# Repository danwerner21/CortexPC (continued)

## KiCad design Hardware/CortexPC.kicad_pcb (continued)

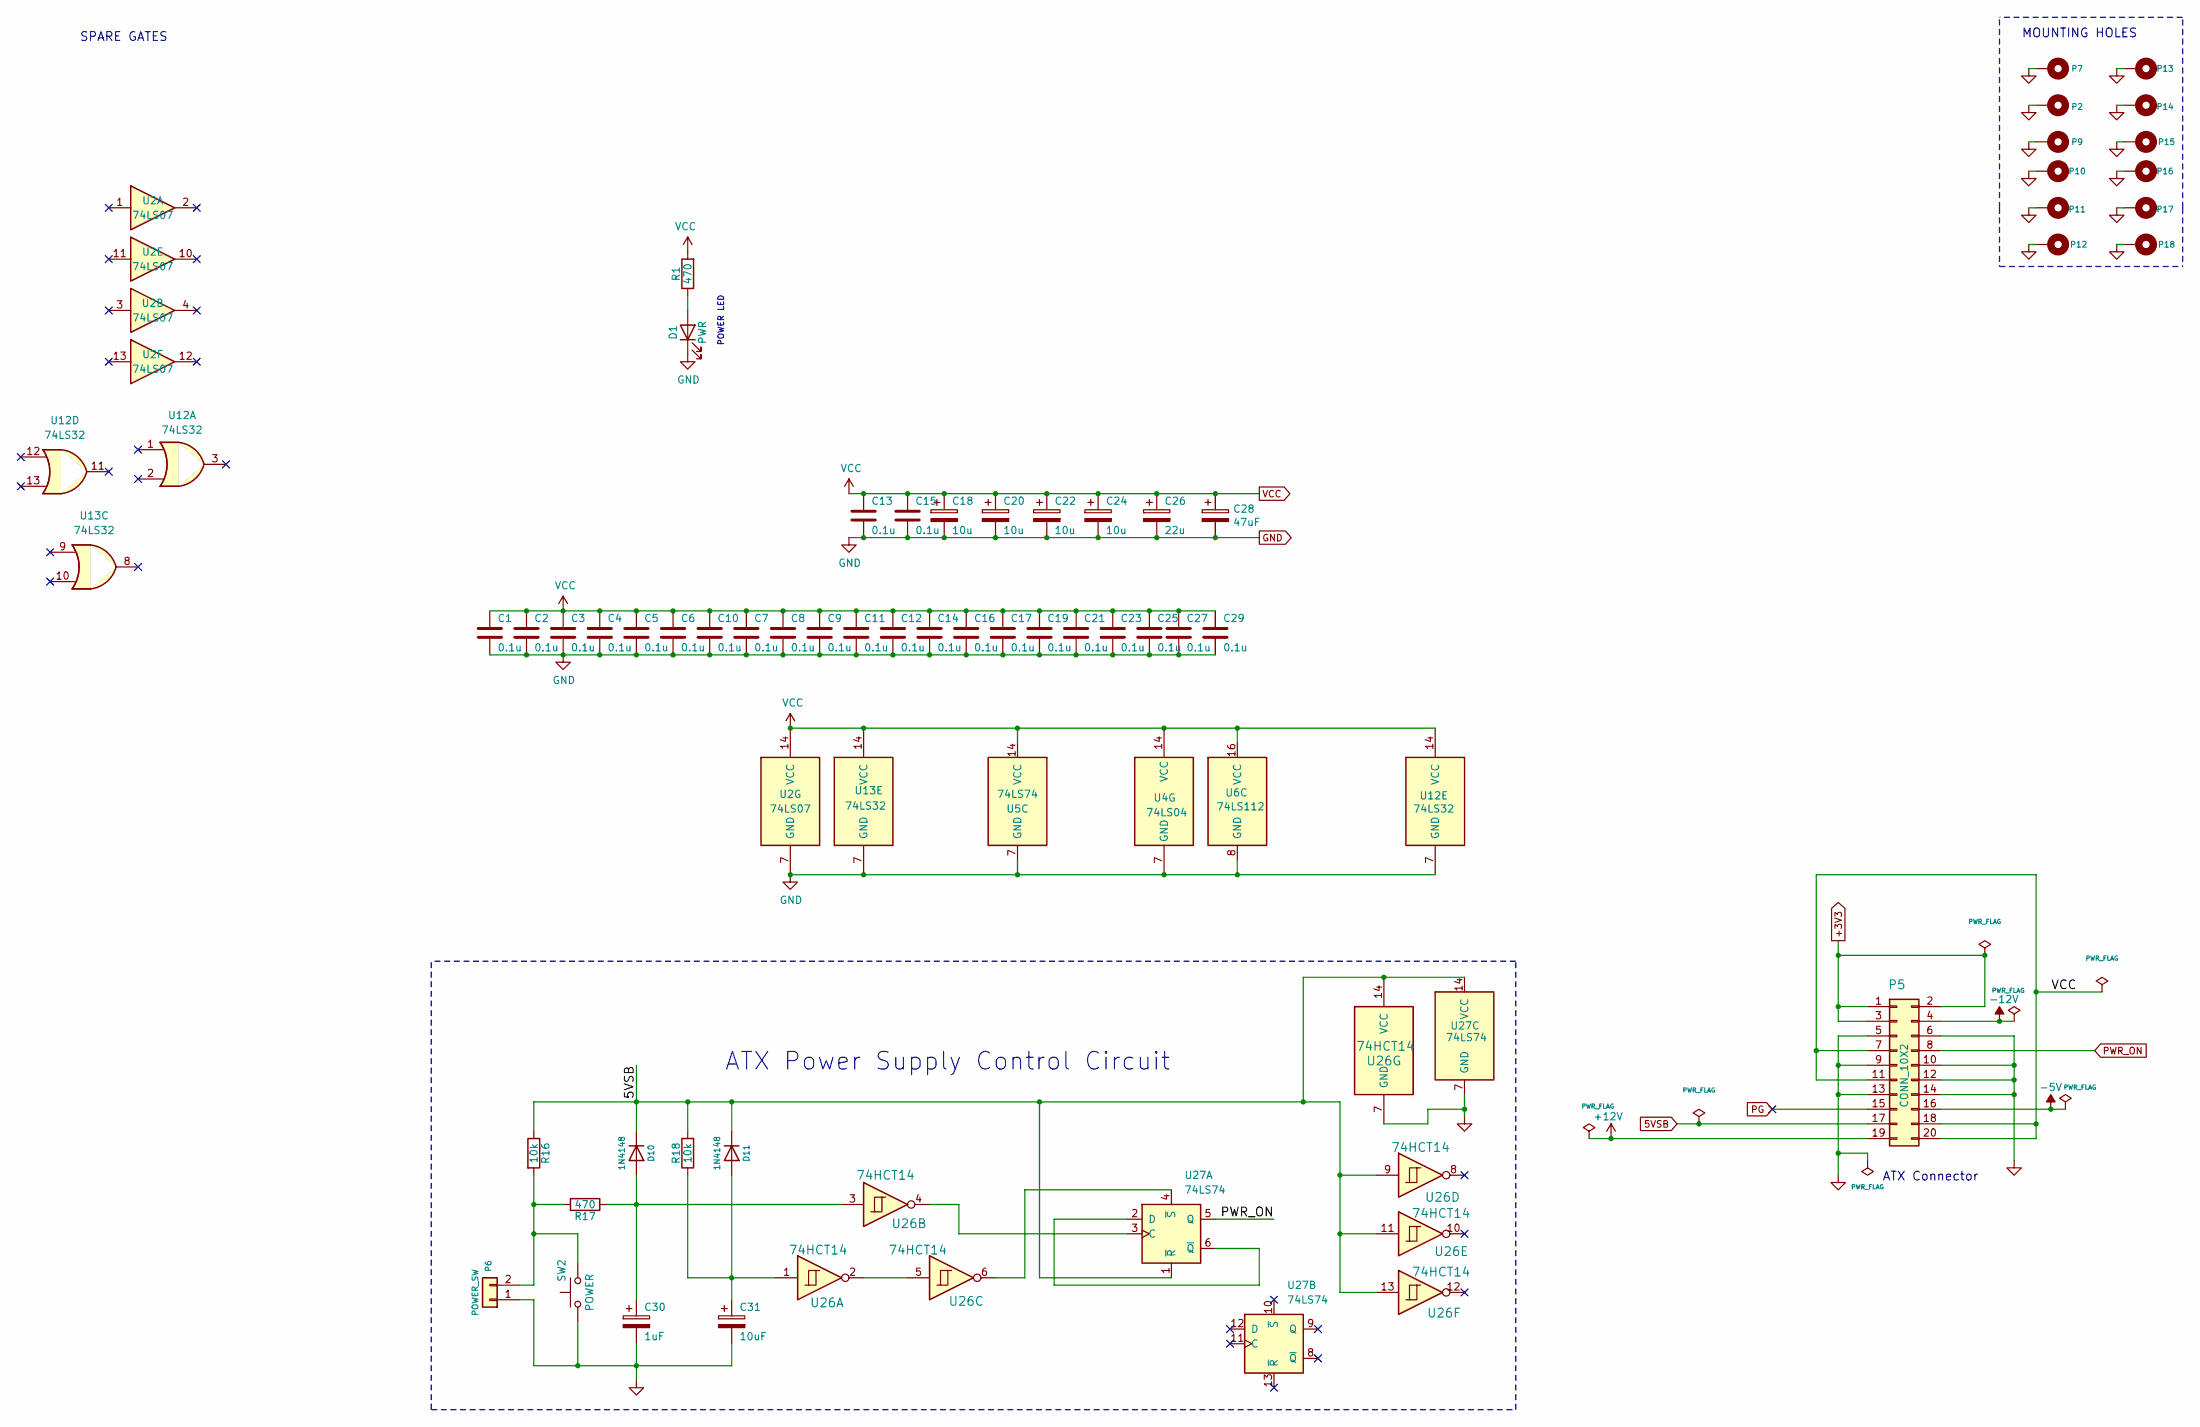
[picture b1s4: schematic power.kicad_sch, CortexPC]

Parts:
C1, C2, C3, C4, C5, C6, C7, C8, C9, C10, C11, C12, C13, C14, C15, C16, C17, C19, C21, C23, C25, C27, C29: 0.1u; STD_DDW_CAP
C18, C20, C22, C24: 10u; STD_DDW_PCAP
C26: 22u; STD_DDW_PCAP
C28: 47uF; STD_DDW_PCAP
C30: 1uF; STD_DDW_PCAP
C31: 10uF; STD_DDW_PCAP
D1: PWR; STD_DDW_LED5
D10, D11: 1N4148; STD_DDW_DIODE
P2, P7, P9, P10, P11, P12, P13, P14, P15, P16, P17, P18: CONN_1; MountingHole_3.2mm_M3_Pad_TopBottom
P5: CONN_10X2; ATXConnector
P6: POWER_SW; STD_DDW_PINHEAD_V_1x02
R1, R17: 470; STD_DDW_RESISTOR
R16, R18: 10k; STD_DDW_RESISTOR
SW2: POWER; STD_DDW_TACTSW
U2: 74LS07; STD_DDW_DIP14
U4: 74LS04; STD_DDW_DIP14
U5, U27: 74LS74; STD_DDW_DIP14
U6: 74LS112; STD_DDW_DIP16
U12, U13: 74LS32; STD_DDW_DIP14
U26: 74HCT14; STD_DDW_DIP14

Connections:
5VSB: D10.1 (K), D11.1 (K), P5.17, R16.1, R18.2, U26.9, U26.11, U26.13, U26.14 (VCC), U27.1 (~R), U27.14 (VCC)
+3V3: P5.1, P5.2, P5.3
+12V: P5.19; also elsewhere on the board
-5V: P5.16; also elsewhere on the board
-12V: P5.4; also elsewhere on the board
GND: C1.2, C2.2, C3.2, C4.2, C5.2, C6.2, C7.2, C8.2, C9.2, C10.2, C11.2, C12.2, C13.2, C14.2, C15.2, C16.2, C17.2, C18.2, C19.2, C20.2, C21.2, C22.2, C23.2, C24.2, C25.2, C26.2, C27.2, C28.2, C29.2, C30.2, C31.2, D1.1 (K), P2.1, P5.5, P5.6, P5.9, P5.10, P5.12, P5.13, P5.14, P6.1, P7.1, P9.1, P10.1, P11.1, P12.1, P13.1, P14.1, P15.1, P16.1, P17.1, P18.1, SW2.1, U2.7 (GND), U4.7 (GND), U5.7 (GND), U6.8 (GND), U12.7 (GND), U13.7 (GND), U26.7 (GND), U27.7 (GND); also elsewhere on the board
unnamed: D1.2 (A), R1.1
unnamed: C30.1, D10.2 (A), R17.1, U26.3
unnamed: C31.1, D11.2 (A), R18.1, U26.1
unnamed: P6.2, R16.2, R17.2, SW2.2
unnamed: U26.2, U26.5
unnamed: U26.4, U27.3 (C)
unnamed: U27.2 (D), U27.6 (~Q)
unnamed: U26.6, U27.4 (~S)
PG: P5.15
PWR_ON: P5.8, U27.5 (Q)
VCC: C1.1, C2.1, C3.1, C4.1, C5.1, C6.1, C7.1, C8.1, C9.1, C10.1, C11.1, C12.1, C13.1, C14.1, C15.1, C16.1, C17.1, C18.1, C19.1, C20.1, C21.1, C22.1, C23.1, C24.1, C25.1, C26.1, C27.1, C28.1, C29.1, P5.7, P5.11, P5.18, P5.20, R1.2, U2.14 (VCC), U4.14 (VCC), U5.14 (VCC), U6.16 (VCC), U12.14 (VCC), U13.14 (VCC); also elsewhere on the board

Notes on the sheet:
POWER LED
ATX Power Supply Control Circuit
MOUNTING HOLES
SPARE GATES
ATX Connector

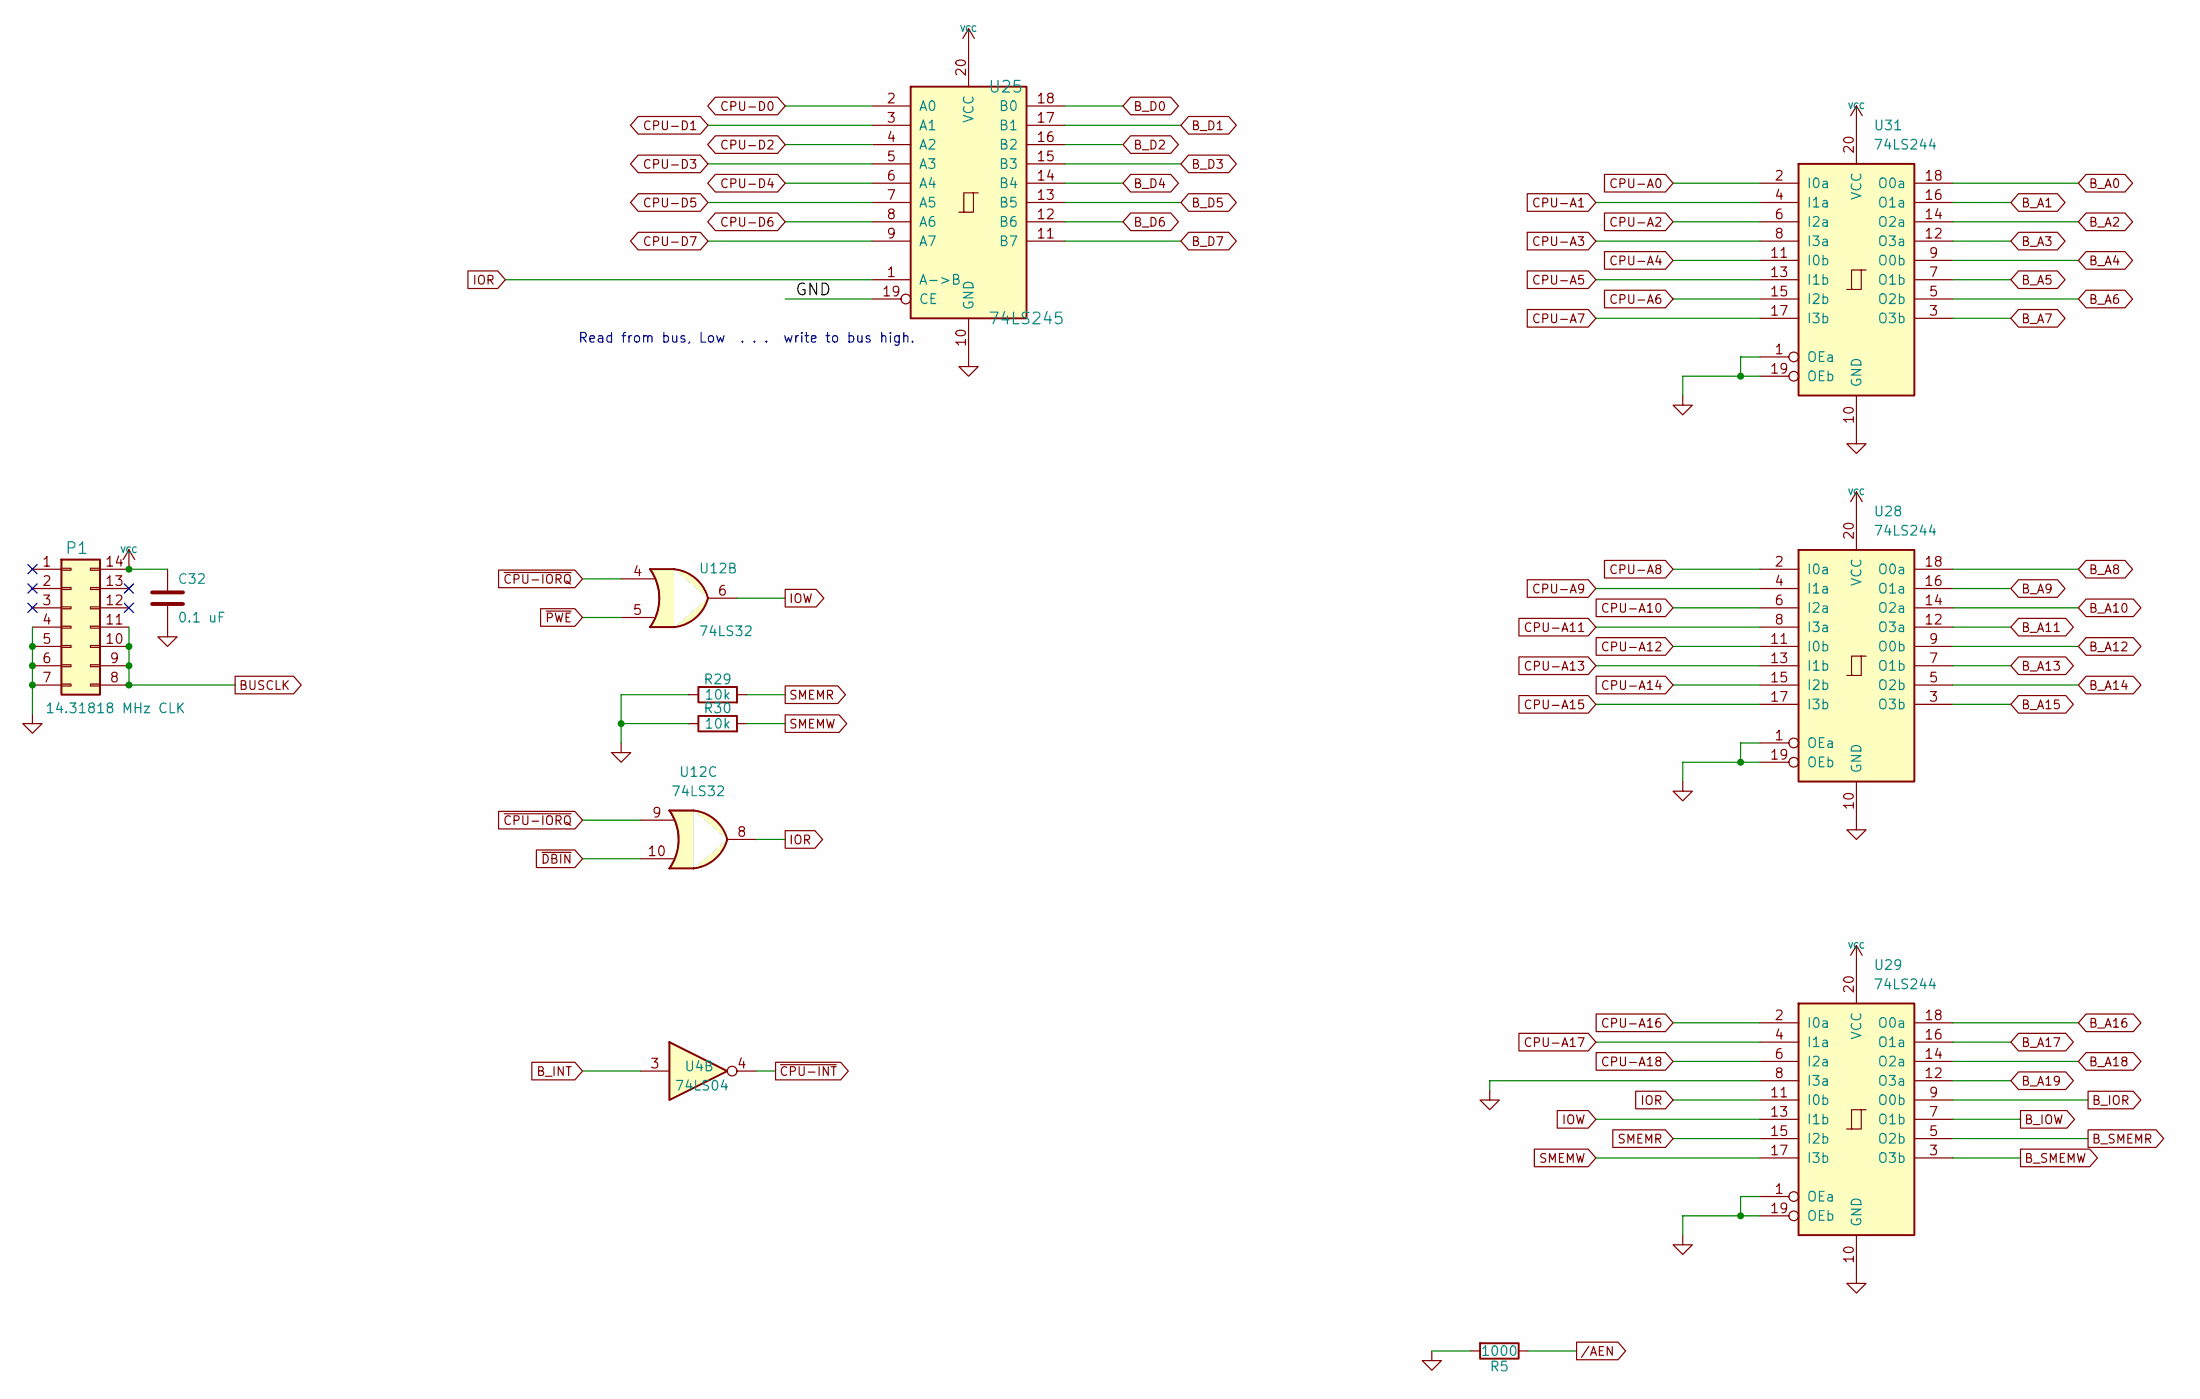
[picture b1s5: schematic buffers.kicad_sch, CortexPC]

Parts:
C32: 0.1 uF; STD_DDW_CAP
P1: 14.31818 MHz CLK; STD_DDW_DIP14
R5: 1000; STD_DDW_RESISTOR
R29, R30: 10k; STD_DDW_RESISTOR
U4: 74LS04; STD_DDW_DIP14
U12: 74LS32; STD_DDW_DIP14
U25: 74LS245; STD_DDW_DIP20
U28, U29, U31: 74LS244; STD_DDW_DIP20

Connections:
BUSCLK: P1.8, P1.9, P1.10, P1.11; also elsewhere on the board
B_A0: U31.18 (O0a); also elsewhere on the board
B_A1: U31.16 (O1a); also elsewhere on the board
B_A2: U31.14 (O2a); also elsewhere on the board
B_A3: U31.12 (O3a); also elsewhere on the board
B_A4: U31.9 (O0b); also elsewhere on the board
B_A5: U31.7 (O1b); also elsewhere on the board
B_A6: U31.5 (O2b); also elsewhere on the board
B_A7: U31.3 (O3b); also elsewhere on the board
B_A8: U28.18 (O0a); also elsewhere on the board
B_A9: U28.16 (O1a); also elsewhere on the board
B_A10: U28.14 (O2a); also elsewhere on the board
B_A11: U28.12 (O3a); also elsewhere on the board
B_A12: U28.9 (O0b); also elsewhere on the board
B_A13: U28.7 (O1b); also elsewhere on the board
B_A14: U28.5 (O2b); also elsewhere on the board
B_A15: U28.3 (O3b); also elsewhere on the board
B_A16: U29.18 (O0a); also elsewhere on the board
B_A17: U29.16 (O1a); also elsewhere on the board
B_A18: U29.14 (O2a); also elsewhere on the board
B_A19: U29.12 (O3a); also elsewhere on the board
B_D0: U25.18 (B0); also elsewhere on the board
B_D1: U25.17 (B1); also elsewhere on the board
B_D2: U25.16 (B2); also elsewhere on the board
B_D3: U25.15 (B3); also elsewhere on the board
B_D4: U25.14 (B4); also elsewhere on the board
B_D5: U25.13 (B5); also elsewhere on the board
B_D6: U25.12 (B6); also elsewhere on the board
B_D7: U25.11 (B7); also elsewhere on the board
B_INT: U4.3; also elsewhere on the board
B_IOR: U29.9 (O0b); also elsewhere on the board
B_IOW: U29.7 (O1b); also elsewhere on the board
B_SMEMR: U29.5 (O2b); also elsewhere on the board
B_SMEMW: U29.3 (O3b); also elsewhere on the board
CPU-A0: U31.2 (I0a); also elsewhere on the board
CPU-A1: U31.4 (I1a); also elsewhere on the board
CPU-A2: U31.6 (I2a); also elsewhere on the board
CPU-A3: U31.8 (I3a); also elsewhere on the board
CPU-A4: U31.11 (I0b); also elsewhere on the board
CPU-A5: U31.13 (I1b); also elsewhere on the board
CPU-A6: U31.15 (I2b); also elsewhere on the board
CPU-A7: U31.17 (I3b); also elsewhere on the board
CPU-A8: U28.2 (I0a); also elsewhere on the board
CPU-A9: U28.4 (I1a); also elsewhere on the board
CPU-A10: U28.6 (I2a); also elsewhere on the board
CPU-A11: U28.8 (I3a); also elsewhere on the board
CPU-A12: U28.11 (I0b); also elsewhere on the board
CPU-A13: U28.13 (I1b); also elsewhere on the board
CPU-A14: U28.15 (I2b); also elsewhere on the board
CPU-A15: U28.17 (I3b); also elsewhere on the board
CPU-A16: U29.2 (I0a); also elsewhere on the board
CPU-A17: U29.4 (I1a); also elsewhere on the board
CPU-A18: U29.6 (I2a); also elsewhere on the board
CPU-D0: U25.2 (A0); also elsewhere on the board
CPU-D1: U25.3 (A1); also elsewhere on the board
CPU-D2: U25.4 (A2); also elsewhere on the board
CPU-D3: U25.5 (A3); also elsewhere on the board
CPU-D4: U25.6 (A4); also elsewhere on the board
CPU-D5: U25.7 (A5); also elsewhere on the board
CPU-D6: U25.8 (A6); also elsewhere on the board
CPU-D7: U25.9 (A7); also elsewhere on the board
GND: C32.2, P1.4, P1.5, P1.6, P1.7, R5.2, R29.1, R30.1, U25.10 (GND), U25.19 (CE), U28.1 (OEa), U28.10 (GND), U28.19 (OEb), U29.1 (OEa), U29.8 (I3a), U29.10 (GND), U29.19 (OEb), U31.1 (OEa), U31.10 (GND), U31.19 (OEb); also elsewhere on the board
IOR: U12.8, U25.1 (A->B), U29.11 (I0b)
IOW: U12.6, U29.13 (I1b)
SMEMR: R29.2, U29.15 (I2b)
SMEMW: R30.2, U29.17 (I3b)
VCC: C32.1, P1.14, U25.20 (VCC), U28.20 (VCC), U29.20 (VCC), U31.20 (VCC); also elsewhere on the board
/AEN: R5.1; also elsewhere on the board
~CPU-INT: U4.4; also elsewhere on the board
~CPU-IORQ: U12.4, U12.9; also elsewhere on the board
~DBIN: U12.10; also elsewhere on the board
~PWE: U12.5; also elsewhere on the board

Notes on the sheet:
Read from bus, Low . . . write to bus high.

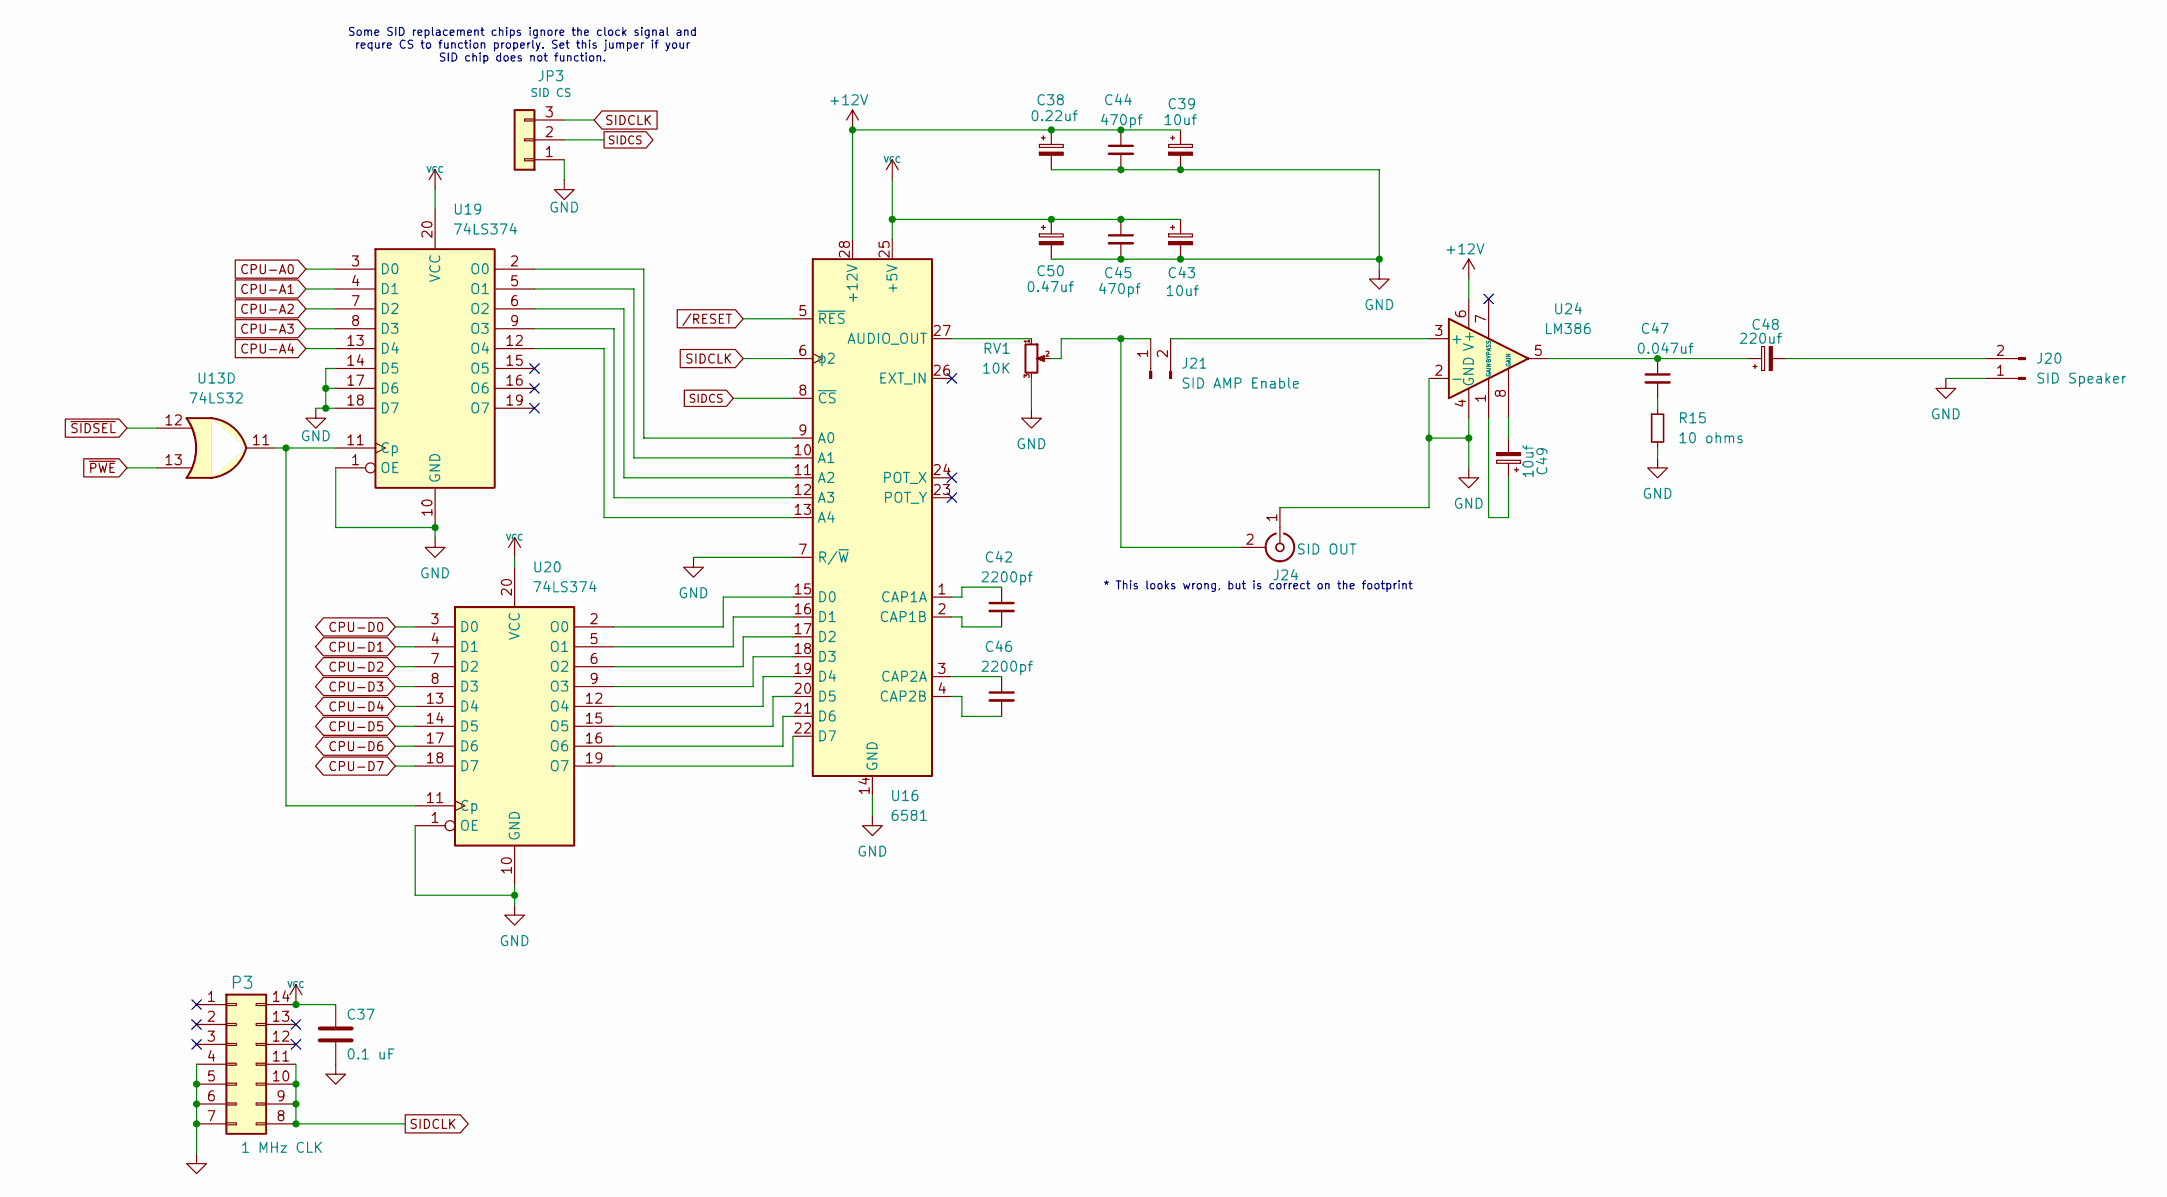
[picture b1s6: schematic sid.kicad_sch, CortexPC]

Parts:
C37: 0.1 uF; STD_DDW_CAP
C38: 0.22uf; STD_DDW_PCAP
C39, C43, C49: 10uf; STD_DDW_PCAP
C42, C46: 2200pf; STD_DDW_CAP
C44, C45: 470pf; STD_DDW_CAP
C47: 0.047uf; STD_DDW_CAP
C48: 220uf; STD_DDW_PCAP
C50: 0.47uf; STD_DDW_PCAP
J20: SID Speaker; STD_DDW_PINHEAD_V_1x02
J21: SID AMP Enable; STD_DDW_PINHEAD_V_1x02
J24: SID OUT; CUI_RCJ-047
JP3: SID CS; STD_DDW_PINHEAD_V_1x03
P3: 1 MHz CLK; STD_DDW_DIP14
R15: 10 ohms; STD_DDW_RESISTOR
RV1: 10K; Potentiometer_Bourns_3386F_Vertical
U13: 74LS32; STD_DDW_DIP14
U16: 6581; STD_DDW_DIP28
U19, U20: 74LS374; STD_DDW_DIP20
U24: LM386; STD_DDW_DIP8

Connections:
+12V: C38.1, C39.1, C44.1, U16.28 (+12V), U24.6 (V+); also elsewhere on the board
CPU-A0: U19.3 (D0); also elsewhere on the board
CPU-A1: U19.4 (D1); also elsewhere on the board
CPU-A2: U19.7 (D2); also elsewhere on the board
CPU-A3: U19.8 (D3); also elsewhere on the board
CPU-A4: U19.13 (D4); also elsewhere on the board
CPU-D0: U20.3 (D0); also elsewhere on the board
CPU-D1: U20.4 (D1); also elsewhere on the board
CPU-D2: U20.7 (D2); also elsewhere on the board
CPU-D3: U20.8 (D3); also elsewhere on the board
CPU-D4: U20.13 (D4); also elsewhere on the board
CPU-D5: U20.14 (D5); also elsewhere on the board
CPU-D6: U20.17 (D6); also elsewhere on the board
CPU-D7: U20.18 (D7); also elsewhere on the board
GND: C37.2, C38.2, C39.2, C43.2, C44.2, C45.2, C50.2, J20.1, J24.1 (In), JP3.1, P3.4, P3.5, P3.6, P3.7, R15.2, RV1.3, U16.7 (R/~W), U16.14 (GND), U19.1 (OE), U19.10 (GND), U19.14 (D5), U19.17 (D6), U19.18 (D7), U20.1 (OE), U20.10 (GND), U24.2 (-), U24.4 (GND); also elsewhere on the board
unnamed: C47.1, C48.1, U24.5
unnamed: C47.2, R15.1
unnamed: C49.1, U24.1 (GAIN)
unnamed: C49.2, U24.8 (GAIN)
unnamed: C48.2, J20.2
unnamed: J21.1, J24.2 (Ext), RV1.2
unnamed: J21.2, U24.3 (+)
unnamed: U16.9 (A0), U19.2 (O0)
unnamed: U16.10 (A1), U19.5 (O1)
unnamed: U16.11 (A2), U19.6 (O2)
unnamed: U16.12 (A3), U19.9 (O3)
unnamed: U16.13 (A4), U19.12 (O4)
unnamed: RV1.1, U16.27 (AUDIO_OUT)
unnamed: C42.1, U16.1 (CAP1A)
unnamed: C42.2, U16.2 (CAP1B)
unnamed: C46.1, U16.3 (CAP2A)
unnamed: C46.2, U16.4 (CAP2B)
unnamed: U16.15 (D0), U20.2 (O0)
unnamed: U16.16 (D1), U20.5 (O1)
unnamed: U16.17 (D2), U20.6 (O2)
unnamed: U16.18 (D3), U20.9 (O3)
unnamed: U16.19 (D4), U20.12 (O4)
unnamed: U16.20 (D5), U20.15 (O5)
unnamed: U16.21 (D6), U20.16 (O6)
unnamed: U16.22 (D7), U20.19 (O7)
unnamed: U13.11, U19.11 (Cp), U20.11 (Cp)
SIDCLK: JP3.3, P3.8, P3.9, P3.10, P3.11, U16.6 (ϕ2)
SIDCS: JP3.2, U16.8 (~CS)
VCC: C37.1, C43.1, C45.1, C50.1, P3.14, U16.25 (+5V), U19.20 (VCC), U20.20 (VCC); also elsewhere on the board
/RESET: U16.5 (~RES); also elsewhere on the board
~PWE: U13.13; also elsewhere on the board
~SIDSEL: U13.12; also elsewhere on the board

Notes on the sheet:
Some SID replacement chips ignore the clock signal and requre CS to function properly. Set this jumper if your SID chip does not function.
* This looks wrong, but is correct on the footprint

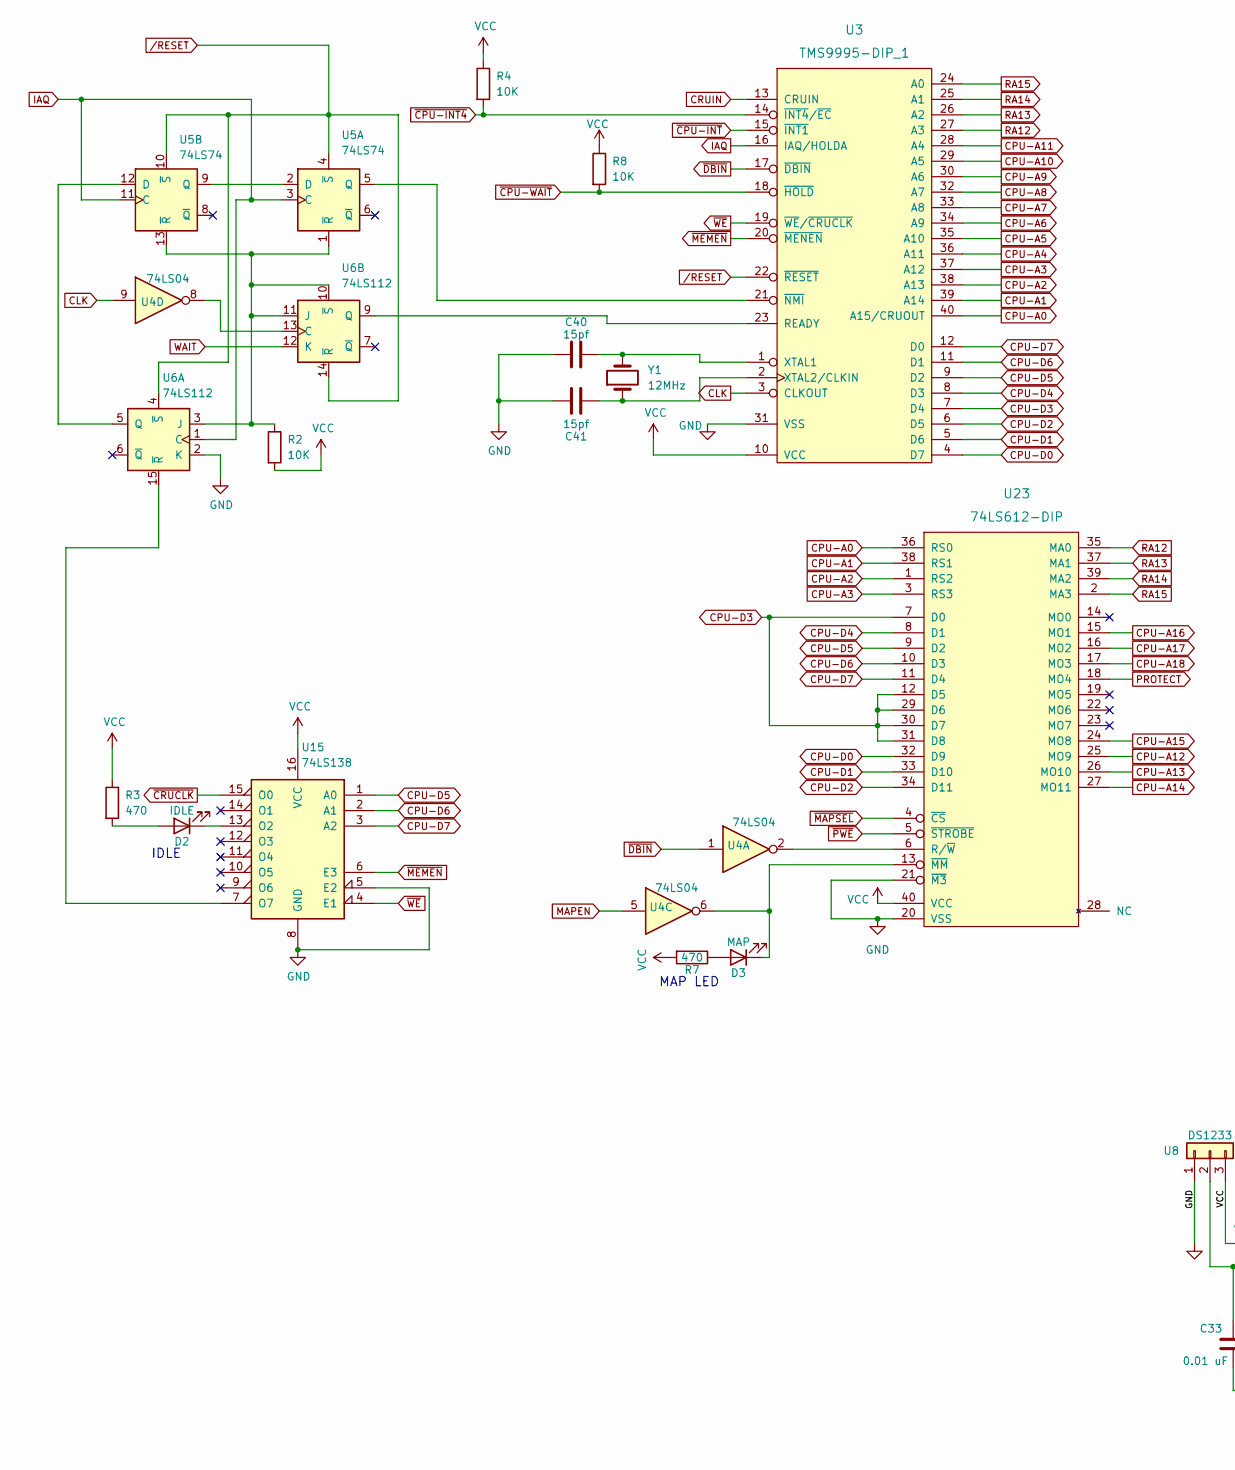
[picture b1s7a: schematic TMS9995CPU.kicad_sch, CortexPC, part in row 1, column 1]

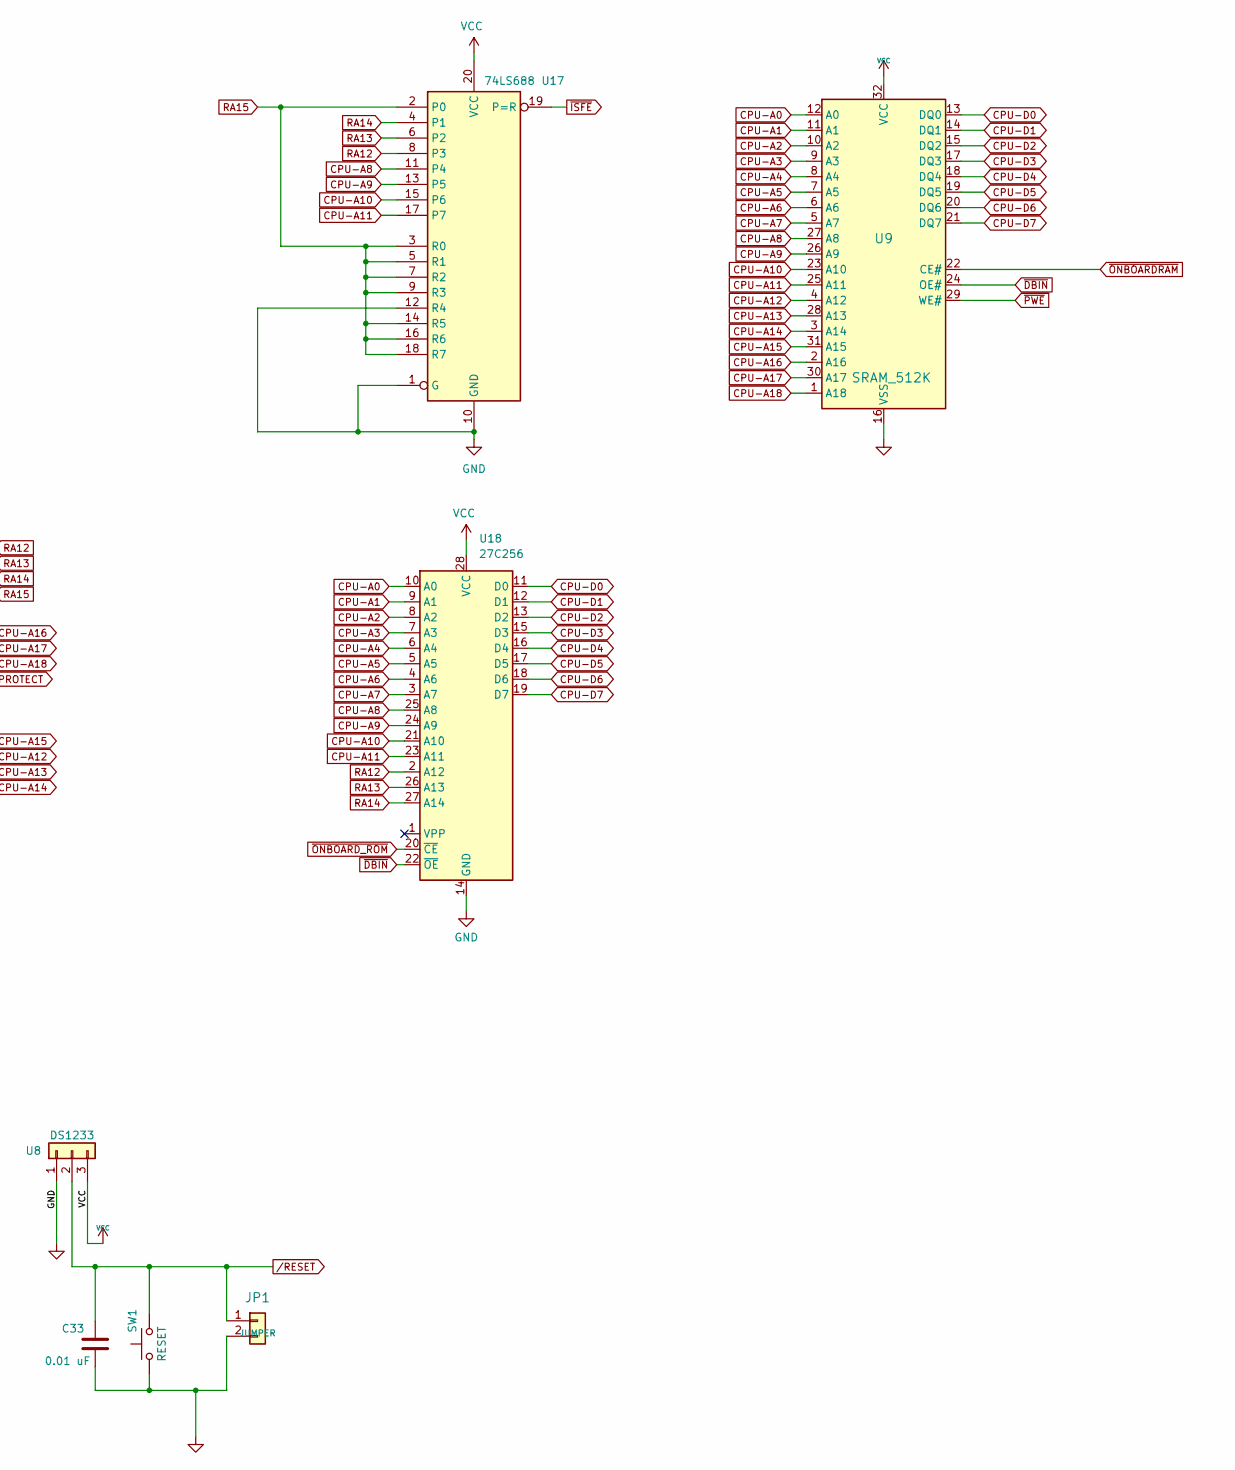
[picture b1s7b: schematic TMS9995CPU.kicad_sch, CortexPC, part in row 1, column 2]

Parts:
C33: 0.01 uF; STD_DDW_CAP
C40, C41: 15pf; STD_DDW_CAP
D2: IDLE; STD_DDW_LED5
D3: MAP; STD_DDW_LED5
JP1: JUMPER; STD_DDW_PINHEAD_V_1x02
R2, R4, R8: 10K; STD_DDW_RESISTOR
R3, R7: 470; STD_DDW_RESISTOR
SW1: RESET; STD_DDW_TACTSW
U3: TMS9995-DIP_1; STD_DDW_DIP40
U4: 74LS04; STD_DDW_DIP14
U5: 74LS74; STD_DDW_DIP14
U6: 74LS112; STD_DDW_DIP16
U8: DS1233; STD_DDW_TO92
U9: SRAM_512K; STD_DDW_DIP32
U15: 74LS138; STD_DDW_DIP16
U17: 74LS688; STD_DDW_DIP20
U18: 27C256; STD_DDW_DIP28
U23: 74LS612-DIP; STD_DDW_DIP40
Y1: 12MHz; STD_DDW_XTAL

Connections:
CLK: U3.3 (CLKOUT), U4.9; also elsewhere on the board
CPU-A0: U3.40 (A15/CRUOUT), U9.12 (A0), U18.10 (A0), U23.36 (RS0); also elsewhere on the board
CPU-A1: U3.39 (A14), U9.11 (A1), U18.9 (A1), U23.38 (RS1); also elsewhere on the board
CPU-A2: U3.38 (A13), U9.10 (A2), U18.8 (A2), U23.1 (RS2); also elsewhere on the board
CPU-A3: U3.37 (A12), U9.9 (A3), U18.7 (A3), U23.3 (RS3); also elsewhere on the board
CPU-A4: U3.36 (A11), U9.8 (A4), U18.6 (A4); also elsewhere on the board
CPU-A5: U3.35 (A10), U9.7 (A5), U18.5 (A5); also elsewhere on the board
CPU-A6: U3.34 (A9), U9.6 (A6), U18.4 (A6); also elsewhere on the board
CPU-A7: U3.33 (A8), U9.5 (A7), U18.3 (A7); also elsewhere on the board
CPU-A8: U3.32 (A7), U9.27 (A8), U17.11 (P4), U18.25 (A8); also elsewhere on the board
CPU-A9: U3.30 (A6), U9.26 (A9), U17.13 (P5), U18.24 (A9); also elsewhere on the board
CPU-A10: U3.29 (A5), U9.23 (A10), U17.15 (P6), U18.21 (A10); also elsewhere on the board
CPU-A11: U3.28 (A4), U9.25 (A11), U17.17 (P7), U18.23 (A11); also elsewhere on the board
CPU-A12: U9.4 (A12), U23.25 (MO9); also elsewhere on the board
CPU-A13: U9.28 (A13), U23.26 (MO10); also elsewhere on the board
CPU-A14: U9.3 (A14), U23.27 (MO11); also elsewhere on the board
CPU-A15: U9.31 (A15), U23.24 (MO8); also elsewhere on the board
CPU-A16: U9.2 (A16), U23.15 (MO1); also elsewhere on the board
CPU-A17: U9.30 (A17), U23.16 (MO2); also elsewhere on the board
CPU-A18: U9.1 (A18), U23.17 (MO3); also elsewhere on the board
CPU-D0: U3.4 (D7), U9.13 (DQ0), U18.11 (D0), U23.32 (D9); also elsewhere on the board
CPU-D1: U3.5 (D6), U9.14 (DQ1), U18.12 (D1), U23.33 (D10); also elsewhere on the board
CPU-D2: U3.6 (D5), U9.15 (DQ2), U18.13 (D2), U23.34 (D11); also elsewhere on the board
CPU-D3: U3.7 (D4), U9.17 (DQ3), U18.15 (D3), U23.7 (D0), U23.12 (D5), U23.29 (D6), U23.30 (D7), U23.31 (D8); also elsewhere on the board
CPU-D4: U3.8 (D3), U9.18 (DQ4), U18.16 (D4), U23.8 (D1); also elsewhere on the board
CPU-D5: U3.9 (D2), U9.19 (DQ5), U15.1 (A0), U18.17 (D5), U23.9 (D2); also elsewhere on the board
CPU-D6: U3.11 (D1), U9.20 (DQ6), U15.2 (A1), U18.18 (D6), U23.10 (D3); also elsewhere on the board
CPU-D7: U3.12 (D0), U9.21 (DQ7), U15.3 (A2), U18.19 (D7), U23.11 (D4); also elsewhere on the board
CRUIN: U3.13 (CRUIN); also elsewhere on the board
GND: C33.2, C40.1, C41.1, JP1.2, SW1.1, U3.31 (VSS), U6.2 (K), U8.1, U9.16 (VSS), U15.5 (E2), U15.8 (GND), U17.1 (G), U17.10 (GND), U17.12 (R4), U18.14 (GND), U23.20 (VSS), U23.21 (~M3); also elsewhere on the board
IAQ: U3.16 (IAQ/HOLDA), U5.3 (C), U5.11 (C), U6.1 (C)
MAPEN: U4.5; also elsewhere on the board
unnamed: D2.2 (A), R3.2
unnamed: D2.1 (K), U15.13 (O2)
unnamed: D3.2 (A), R7.1
unnamed: D3.1 (K), U4.6, U23.13 (~MM)
unnamed: U3.23 (READY), U6.9 (Q)
unnamed: C40.2, U3.1 (XTAL1), Y1.2
unnamed: C41.2, U3.2 (XTAL2/CLKIN), Y1.1
unnamed: U3.21 (~NMI), U5.5 (Q)
unnamed: U5.2 (D), U5.9 (Q)
unnamed: R2.1, U5.1 (~R), U5.13 (~R), U6.3 (J), U6.10 (~S), U6.11 (J)
unnamed: U5.12 (D), U6.5 (Q)
unnamed: U4.8, U6.13 (C)
unnamed: U6.15 (~R), U15.7 (O7)
unnamed: U4.2, U23.6 (R/~W)
PROTECT: U23.18 (MO4); also elsewhere on the board
RA12: U3.27 (A3), U17.8 (P3), U18.2 (A12), U23.35 (MA0)
RA13: U3.26 (A2), U17.6 (P2), U18.26 (A13), U23.37 (MA1)
RA14: U3.25 (A1), U17.4 (P1), U18.27 (A14), U23.39 (MA2)
RA15: U3.24 (A0), U17.2 (P0), U17.3 (R0), U17.5 (R1), U17.7 (R2), U17.9 (R3), U17.14 (R5), U17.16 (R6), U17.18 (R7), U23.2 (MA3); also elsewhere on the board
VCC: R2.2, R3.1, R4.1, R7.2, R8.1, U3.10 (VCC), U8.3, U9.32 (VCC), U15.16 (VCC), U17.20 (VCC), U18.28 (VCC), U23.40 (VCC); also elsewhere on the board
WAIT: U6.12 (K); also elsewhere on the board
/RESET: C33.1, JP1.1, SW1.2, U3.22 (~RESET), U5.4 (~S), U5.10 (~S), U6.4 (~S), U6.14 (~R), U8.2; also elsewhere on the board
~CPU-INT4: R4.2, U3.14 (~INT4/~EC); also elsewhere on the board
~CPU-INT: U3.15 (~INT1); also elsewhere on the board
~CPU-WAIT: R8.2, U3.18 (~HOLD)
~CRUCLK: U15.15 (O0); also elsewhere on the board
~DBIN: U3.17 (~DBIN), U4.1, U9.24 (OE#), U18.22 (~OE); also elsewhere on the board
~ISFE: U17.19 (P=R); also elsewhere on the board
~MAPSEL: U23.4 (~CS); also elsewhere on the board
~MEMEN: U3.20 (~MENEN), U15.6 (E3); also elsewhere on the board
~ONBOARDRAM: U9.22 (CE#); also elsewhere on the board
~ONBOARD_ROM: U18.20 (~CE); also elsewhere on the board
~PWE: U9.29 (WE#), U23.5 (~STROBE); also elsewhere on the board
~WE: U3.19 (~WE/~CRUCLK), U15.4 (E1); also elsewhere on the board

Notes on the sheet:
MAP LED
IDLE
